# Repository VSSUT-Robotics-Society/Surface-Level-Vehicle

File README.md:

# Surface Level Vehicle (SLV)

An autonomous surface water robot designed for environmental monitoring, research, and rescue operations.

---

## Table of Contents
1. [Overview](#overview)
2. [Our Goals](#our-goals)
3. [What We Currently Use](#what-we-currently-use)
    - [Hardware](#hardware)
    - [Software](#software)
    - [Packages](#packages)
4. [How to Run the Project](#how-to-run-the-project)
    - [Installation](#installation)
5. [Problems Currently Being Faced](#problems-currently-being-faced)
6. [Bill of Materials Required](#bill-of-materials-required)
7. [Future Applications/Features](#future-applicationsfeatures)
8. [References](#references)

---

## Overview

The Surface Level Vehicle (SLV) is an unmanned watercraft designed for surface-level operations. It incorporates a lightweight, durable aluminum extrusion frame for structural support, enhancing stability, modularity, and ease of assembly. Powered by four BLDC motors and equipped with GPS for autonomous navigation, the SLV is built for efficient and precise aquatic missions.

---

## Our Goals

- Develop a cost-effective and modular surface vehicle.
- Enable autonomous water navigation using GPS.
- Support various environmental, research, and safety applications.
- Ensure stability, durability, and ease of customization.

---

## What We Currently Use

### Hardware

- Aluminum extrusion frame  
- 4 × High-RPM BLDC motors with waterproof propellers  
- 2 × Air-filled PVC pipes (floatation)  
- GPS module  
- Rechargeable battery pack  
- Waterproof enclosures

### Software

- Arduino IDE (for motor and GPS control)  
- Mission planning software (e.g., QGroundControl or custom path planner)

### Packages

- Easy navigation and motor control libraries (to be listed if available)

---

## How to Run the Project

### Installation

1. Connect the GPS and motor controllers to the microcontroller.
2. Upload the control code using Arduino IDE.
3. Ensure all connections are waterproof and secured.
4. Calibrate motors and GPS before deployment.

---

## Problems Currently Being Faced

- Fine-tuning GPS accuracy for precise waypoint navigation.
- Ensuring reliable waterproofing in high humidity or splash zones.
- Battery life optimization during long missions.

---

## Bill of Materials Required

| Item                     | Quantity | Description                       |
|--------------------------|----------|-----------------------------------|
| Aluminum extrusions      |   xN     | Main structural frame             |
| BLDC Motors (Waterproof) |    4     | Propulsion                        |
| Propellers               |    4     | Attached to motors                |
| PVC Pipes (Floatation)   |    2     | Buoyancy and stability            |
| GPS Module               |    1     | Navigation                        |
| Rechargeable Battery     |    1     | Power source                      |
| Waterproof Enclosure     |    N     | Electronics protection            |

---

## Future Applications/Features

- Solar power integration using the flat frame surface  
- Mounting of advanced sensors (LIDAR, sonar, turbidity, etc.)  
- Hydrodynamic optimization of float structures  
- Modular add-ons for different missions (sample collectors, probes)

---

## References

- Internal project documentation  
- Arduino & sensor datasheets  
- Research on autonomous surface vehicles

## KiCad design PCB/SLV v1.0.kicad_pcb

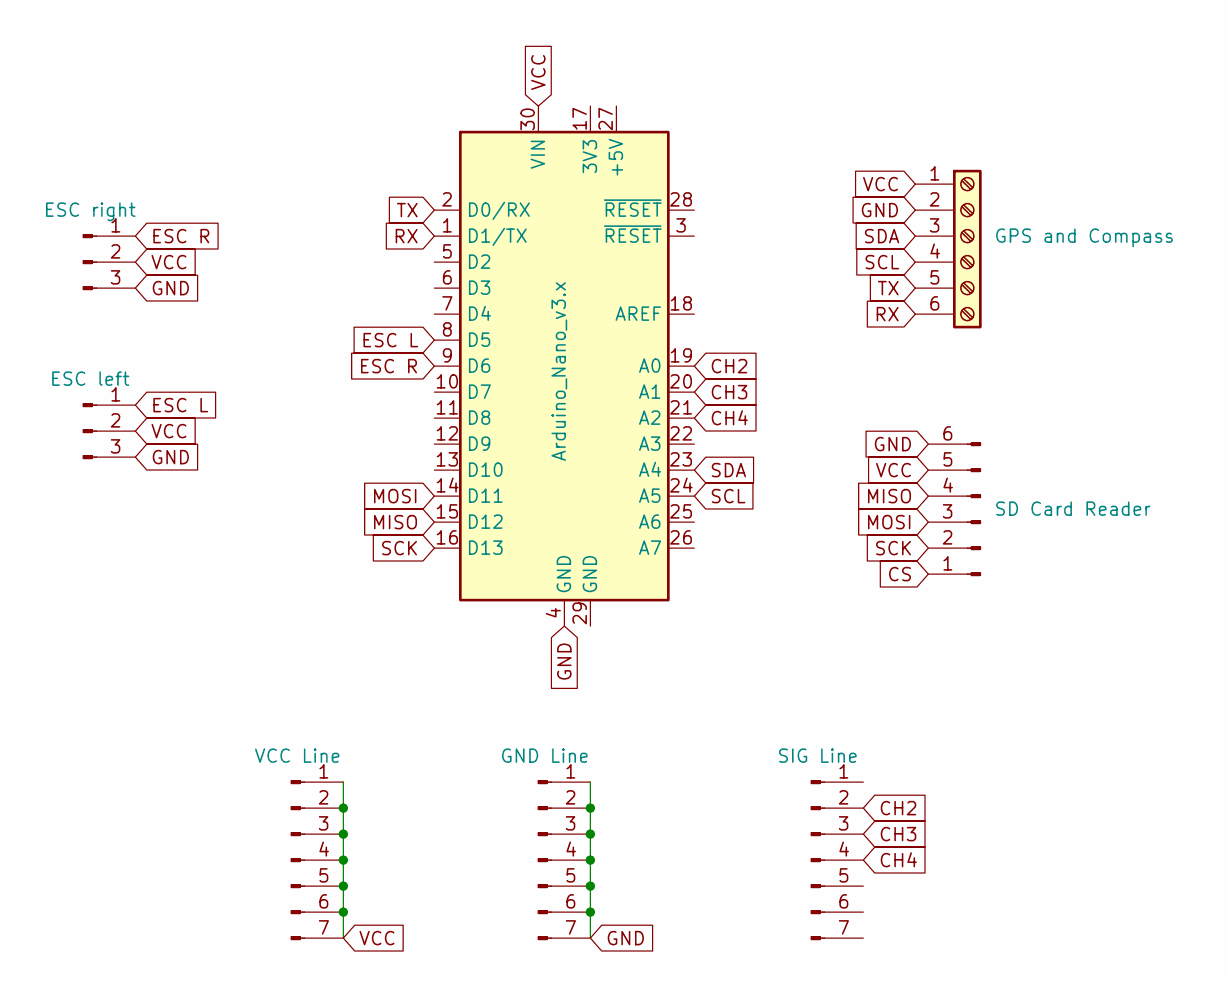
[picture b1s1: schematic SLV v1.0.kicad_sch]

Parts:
A1: Arduino_Nano_v3.x; Arduino_Nano
J1: GPS and Compass; TerminalBlock_bornier-6_P5.08mm
J2: SD Card Reader; PinHeader_1x06_P2.54mm_Vertical
J3: ESC left; PinHeader_1x03_P2.54mm_Vertical
J4: ESC right; PinHeader_1x03_P2.54mm_Vertical
J5: VCC Line; PinHeader_1x07_P2.54mm_Vertical
J6: GND Line; PinHeader_1x07_P2.54mm_Vertical
J7: SIG Line; PinHeader_1x07_P2.54mm_Vertical

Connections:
CH2: A1.19 (A0), J7.2
CH3: A1.20 (A1), J7.3
CH4: A1.21 (A2), J7.4
CS: J2.1
ESC L: A1.8 (D5), J3.1
ESC R: A1.9 (D6), J4.1
GND: A1.4 (GND), J1.2, J2.6, J3.3, J4.3, J6.1, J6.2, J6.3, J6.4, J6.5, J6.6, J6.7
MISO: A1.15 (D12), J2.4
MOSI: A1.14 (D11), J2.3
RX: A1.1 (D1/TX), J1.6
SCK: A1.16 (D13), J2.2
SCL: A1.24 (A5), J1.4
SDA: A1.23 (A4), J1.3
TX: A1.2 (D0/RX), J1.5
VCC: A1.30 (VIN), J1.1, J2.5, J3.2, J4.2, J5.1, J5.2, J5.3, J5.4, J5.5, J5.6, J5.7

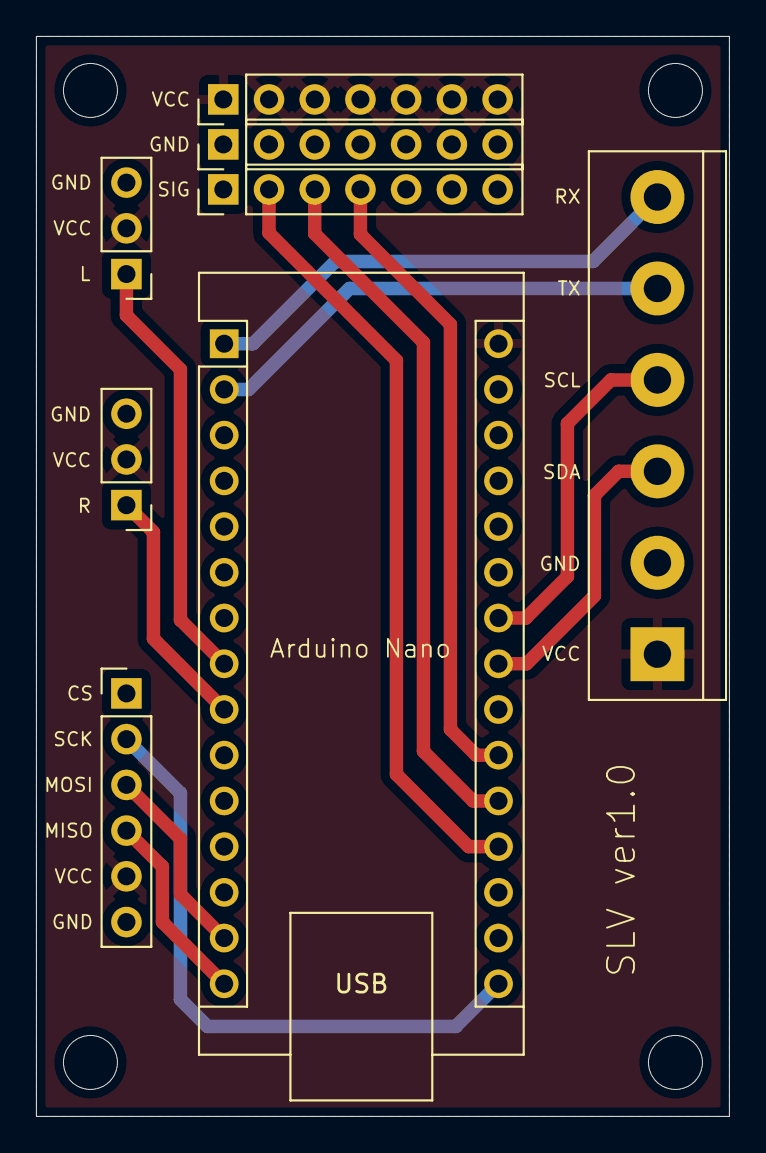
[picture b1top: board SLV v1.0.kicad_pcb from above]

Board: 2 copper layers, 38.5 x 60.0 mm, 8 parts (0 on the bottom side), 14 nets.

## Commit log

2025-06-18 Surface Level Vehicle
2025-06-18 Added Readme.md
2025-07-04 Restructured files hierarchy
2025-07-07 First draft of PCB Design completed
